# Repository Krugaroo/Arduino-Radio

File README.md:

# Arduino Radio
 A simple solar powered FM radio project

 *Note: The software included in this project is complete and can be used to flash onto an Arduino directly. The final project is intended to be on a custom PCB with an AtTiny-85 microcontroller.
 The PCB design is on its first revision, and requires some workaround. I will finish the PCB and add a proper readme in the future.*
 
 This project is a simple solar power radio that was to be used in a volunteering project via Engineers without Borders to teach and engage children with science and engineering.
 It was intended to be a fun and useful project for schools kids on our yearly trip to Mozambique to teach Engineering [https://www.ewbnl.org/schools-of-the-future/]. However due to Covid-19 the execution is currently postphoned.
 
 I have made the PCB design and Arduino software available freely in the hope that it might still be of use.
 
 The project uses a simple module (RDA5807) that can be bought cheaply and controlled over I2C using a microcontroller (i.e Arduino). The audio is amplified with an amplifier (PAM8403). I have included a BOM list for reference.
 The total cost at single units is less than 10 Euro.
 
 # How it works
 The radio can search for channels by keeping the scan button pressed. Once the desired channel is found let go of the button.
 The volume can be increased/decreased by pressing the volume up and down buttons
 Once a channel and volume is selected it will be stored in the EEPROM so it does not need to be tuned again when power is restored.

 # Tips
 1. The PCB design is nearly complete, but was put on hold. As such I plan to still work on it. Let me know if there is interest to do so. The PCB is workable but requires a workaround, because of the switch to the AtTiny 85
 2. When soldering the RDA5807 it is a lot easier to do it upside down so the crystal and small chip is facing down, this exposes the pads much better.
 3. If you have trouble getting it to work make sure the crystal on the RDA5807 is not shorted. This is quite easily to do accidentally when soldering.
 4. For the antenna any piece of wire will do, it will probably also work okayish without one.
 
 If you run into any problems please post an issue in Github!

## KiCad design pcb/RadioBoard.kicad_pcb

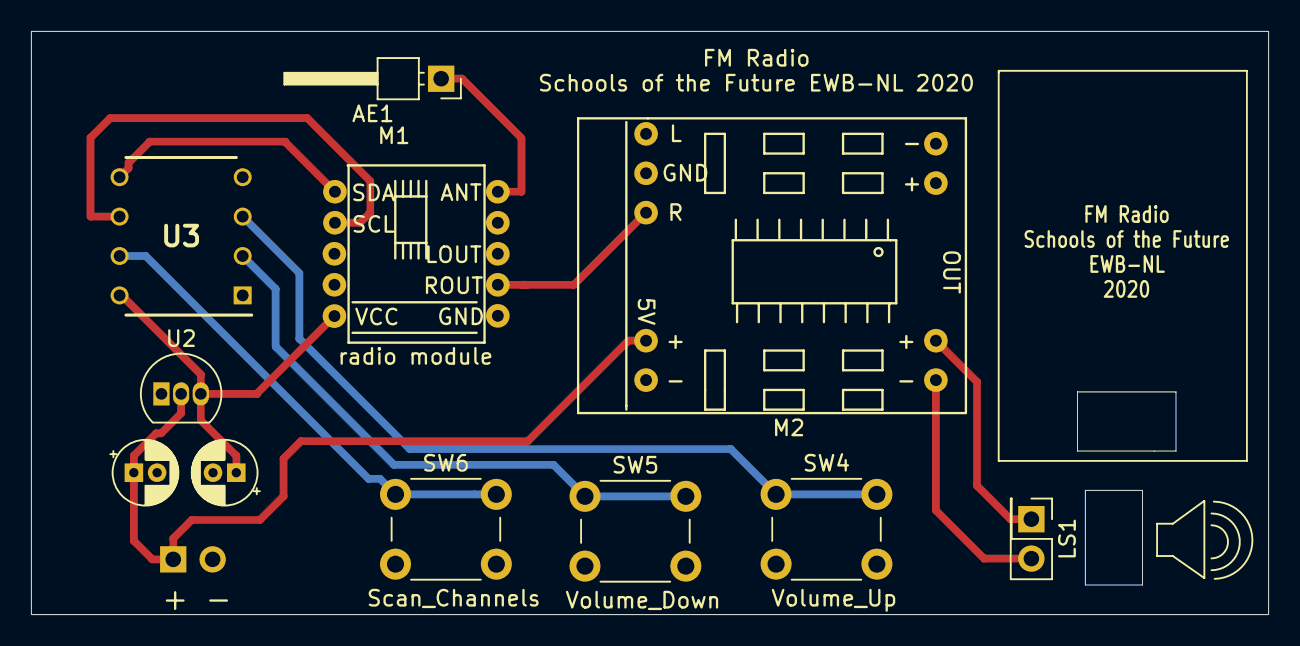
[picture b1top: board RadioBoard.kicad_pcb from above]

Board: 2 copper layers, 79.8 x 37.6 mm, 12 parts (1 on the bottom side), 12 nets.

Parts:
AE1: Antenna; PinHeader_1x01_P2.54mm_Horizontal
C4, C5: 1 uF; CP_Radial_D4.0mm_P1.50mm
J1: Power Input; PinHeader_1x02_P2.54mm_Vertical
LS1: Speaker; PinHeader_2x01_P2.54mm_Vertical
M1: module_radio_RDA5807M
M2: module_audioamp_PAM8403
SW4: Volume_Up; SW_PUSH_6mm
SW5: Volume_Down; SW_PUSH_6mm
SW6: Scan_Channels; SW_PUSH_6mm
U2: MCP1700-3002E_TO92; TO-92_Inline
U3: ATtiny13V-10PU; DIP794W56P254L959H533Q8N

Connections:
GND: C4.2, C5.2, J1.2, M1.10, M2.2, M2.5, SW4.2, SW5.2, SW6.2, U2.1, U3.4
unnamed: AE1.1, M1.6
unnamed: C5.1, M1.5, U2.3, U3.8
unnamed: LS1.1, M2.8
unnamed: LS1.2, M2.9
unnamed: M1.1, U3.5
unnamed: M1.2, U3.6
unnamed: M1.9, M2.3
unnamed: SW4.1, U3.3
unnamed: SW5.1, U3.2
unnamed: SW6.1, U3.7
OUTPUT_SOUND: C4.1, J1.1, M2.4, U2.2

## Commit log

2020-10-11 Initial Commit
    Initial Commit of the Radio Arduino project
2020-10-11 Added Picture
    Added a picture of the assembled radio
